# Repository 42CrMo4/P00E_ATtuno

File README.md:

# KiCad ATtuno Dev board

The ATtuno is a dev board for ATtiny 1 series microcontroller, loosely based on the UNO form factor. 

## Description

The ATtuno is an excellent starting point for those looking to explore the ATtiny 1 series microcontroller platform. 
Inspired by the familiar Arduino Uno form factor, this board offers a user-friendly approach to working with ATtiny Series 1 MCUs.
Key features:

- Arduino Uno-inspired layout
- Generous board size for comfortable handling
- Robust Wago clamping pin headers for secure connections
- Designed for quick start and rapid prototyping
- 3.3V and 5V compatible

This dev board bridges the gap between the popular Arduino ecosystem and the powerful, efficient ATtiny Series 1 microcontrollers. 
Its thoughtful design allows both beginners and experienced makers to quickly dive into projects without the need for delicate handling or specialized tools.

### Goal

The goal of the project will be:
- [ ] **undefined** - not known what the project will bring 
- [ ] **learn** - personally learn something new, no usefull outcome expected
- [ ] **prototype** - a working prototype or mvp
- [x] **80-20-rule** - 80% outcome with 20% effort
- [ ] **Product** - lets see :wink:

## KiCanvas 

view the project files in the browaser without downloading or installing anything via [KiCanvas](https://kicanvas.org)

[Main branche - Development](https://kicanvas.org/?github=https%3A%2F%2Fgithub.com%2F42CrMo4%2FP00E_ATtuno)

[v3.0](https://kicanvas.org/?github=https%3A%2F%2Fgithub.com%2F42CrMo4%2FP00E_ATtuno%2Ftree%2Fv3.0)

[v2.0](https://kicanvas.org/?github=https%3A%2F%2Fgithub.com%2F42CrMo4%2FP00E_ATtuno%2Ftree%2Fv2.0)

[v1.0](https://kicanvas.org/?github=https%3A%2F%2Fgithub.com%2F42CrMo4%2FP00E_ATtuno%2Ftree%2Fv1.0)

## Rendering (V3.0)

|     Font      |     Back      |
| ------------- | ------------- |
|||

If you are looking for the latest Release with all the artifacts please visit the 

## Rendering & BOM (Dev)

The renderings and BOM below are the uptodate state of the main branche.

| Font                                                                    | Back                                                                      |
|-------------------------------------------------------------------------|---------------------------------------------------------------------------|
|  |  |

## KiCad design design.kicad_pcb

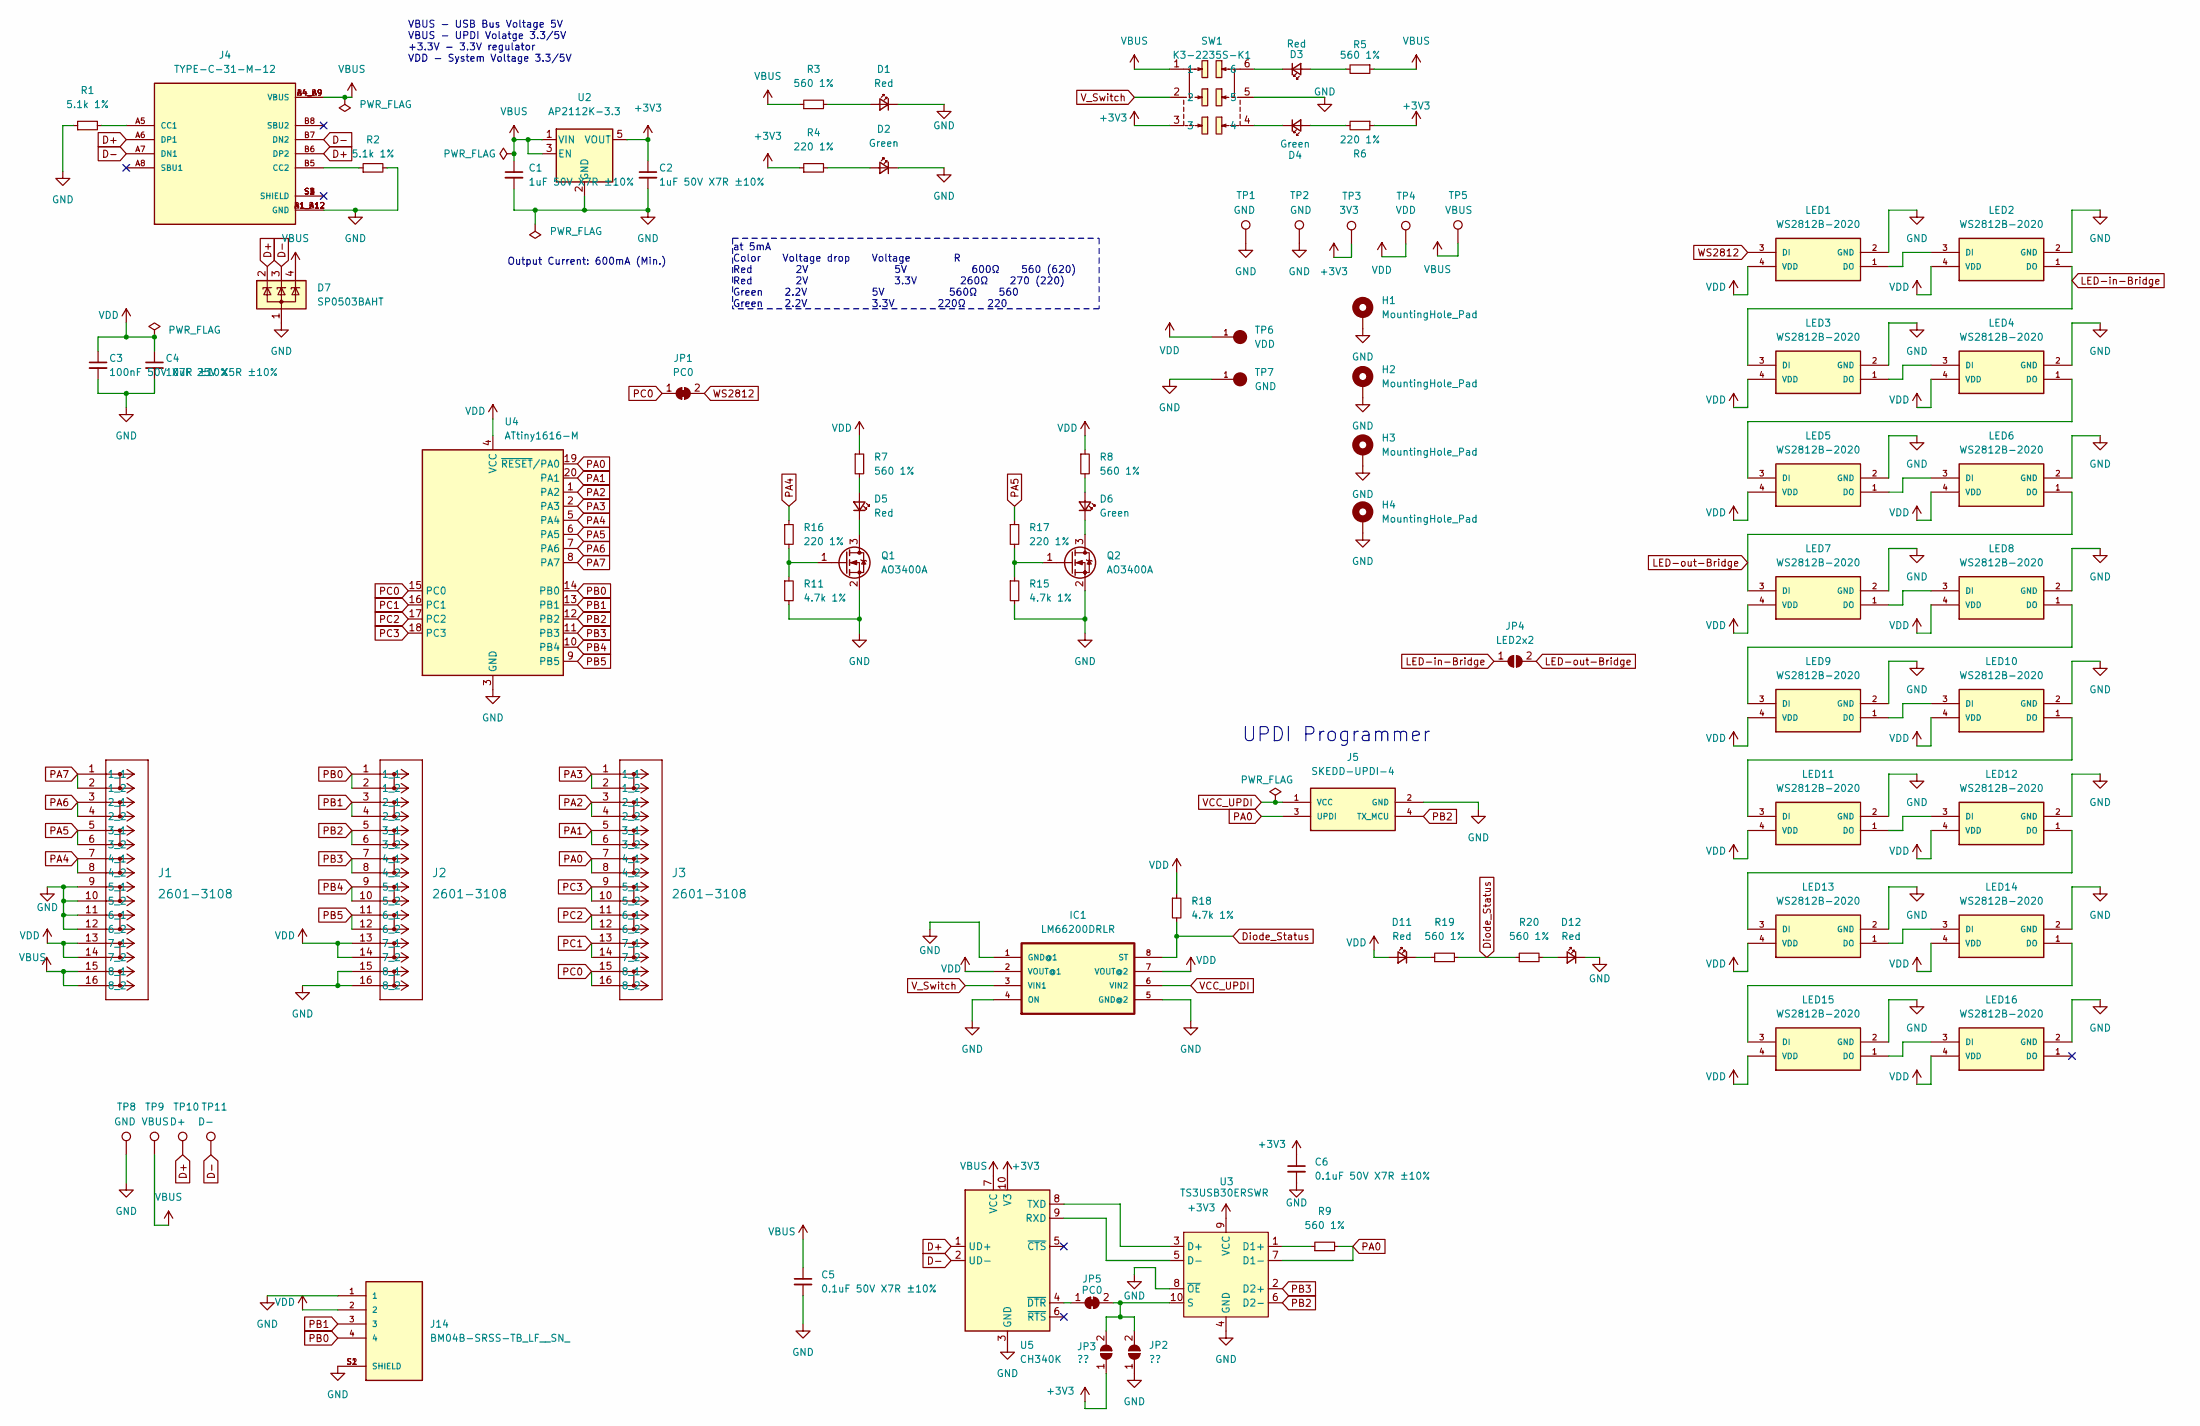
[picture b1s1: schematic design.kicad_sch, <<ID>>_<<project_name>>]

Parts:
C1, C2: 1uF 50V X7R ±10%; C_0805_2012Metric; MANUFACTURER_PART_NUMBER CL21B105KBFNNNE; JLCPCB C28323
C3: 100nF 50V X7R ±10%; C_0805_2012Metric; MANUFACTURER_PART_NUMBER CC0805KRX7R9BB104; JLCPCB C49678
C4: 10uF 25V X5R ±10%; C_0805_2012Metric; MANUFACTURER_PART_NUMBER CL21A106KAYNNNE; JLCPCB C15850
C5, C6: 0.1uF 50V X7R ±10%; C_0805_2012Metric; MANUFACTURER_PART_NUMBER CL21B105KBFNNNE; JLCPCB C28323
D1, D3, D5, D11, D12: Red; LED_0805_2012Metric; MANUFACTURER_PART_NUMBER NCD0805R1; JLCPCB C84256
D2, D4, D6: Green; LED_0805_2012Metric; MANUFACTURER_PART_NUMBER KT-0805G; JLCPCB C2297
D7: SP0503BAHT; SOT-143; MANUFACTURER_PART_NUMBER SP0503BAHTG; JLCPCB C3040626
H1, H2, H3, H4: MountingHole_Pad; MountingHole_2.7mm_M2.5_Pad_Via
IC1: LM66200DRLR; LM66200DRLR_SOT8
J1, J2, J3: 2601-3108; CONN8_2601-3108_WAG
J4: TYPE-C-31-M-12; TYPE-C-31-M-12_HRO_TYPE-C-31-M-12; PARTREV 2020.12.08; JLCPCB C165948
J5: SKEDD-UPDI-4
J14: BM04B-SRSS-TB_LF__SN_; BM04B-SRSS-TB_LF__SN__JST_BM04B-SRSS-TB_LF__SN_; PARTREV N/A; JLCPCB C160390
JP1, JP5: PC0; SolderJumper-2_P1.3mm_Bridged_Pad1.0x1.5mm
JP2, JP3: ??; SolderJumper-2_P1.3mm_Open_Pad1.0x1.5mm
JP4: LED2x2; SolderJumper-2_P1.3mm_Open_Pad1.0x1.5mm
LED1, LED2, LED3, LED4, LED5, LED6, LED7, LED8, LED9, LED10, LED11, LED12, LED13, LED14, LED15, LED16: WS2812B-2020; WS2812B2020; MANUFACTURER_PART_NUMBER WS2812B-2020; JLCPCB C965555
Q1, Q2: AO3400A; SOT-23; MANUFACTURER_PART_NUMBER AO3400A; JLCPCB C20917
R1, R2: 5.1k 1%; R_0805_2012Metric; MANUFACTURER_PART_NUMBER C27834; JLCPCB C27834
R3, R5, R7, R8, R9, R19, R20: 560 1%; R_0805_2012Metric; MANUFACTURER_PART_NUMBER 0805W8F5600T5E; JLCPCB C28636
R4, R6, R16, R17: 220 1%; R_0805_2012Metric; MANUFACTURER_PART_NUMBER 0805W8F2200T5E; JLCPCB C17557
R11, R15, R18: 4.7k 1%; R_0805_2012Metric; MANUFACTURER_PART_NUMBER 0805W8F4701T5E; JLCPCB C17673
SW1: K3-2235S-K1; easyeda2kicad_SW-SMD_K3-2235S-K1; MANUFACTURER_PART_NUMBER K3-2235S-K1; LCSC Part C145845
TP1, TP2, TP8: GND; TestPoint_Pad_D2.5mm
TP3: 3V3; TestPoint_Pad_D2.5mm
TP4: VDD; TestPoint_Pad_D2.5mm
TP5, TP9: VBUS; TestPoint_Pad_D2.5mm
TP6: VDD; RCWCTE_TP420X150; PARTREV 1/06/14
TP7: GND; RCWCTE_TP420X150; PARTREV 1/06/14
TP10: D+; TestPoint_Pad_D2.5mm
TP11: D-; TestPoint_Pad_D2.5mm
U2: AP2112K-3.3; SOT-23-5; MANUFACTURER_PART_NUMBER TPAP2112K-3.3TRG1; JLCPCB C3021085
U3: TS3USB30ERSWR; UQFN-10_1.4x1.8mm_P0.4mm
U4: ATtiny1616-M; ATTINY1616-MFR_QFN40P300X300X90-21N; MANUFACTURER_PART_NUMBER ATTINY1616-MNR; JLCPCB C507118
U5: CH340K; SSOP-10-1EP_3.9x4.9mm_P1mm_EP2.1x3.3mm

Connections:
+3V3: C2.1, C6.1, JP3.1 (A), R4.1, R6.1, SW1.3, TP3.1, U2.5 (VOUT), U3.9 (VCC), U5.10 (V3)
D+: D7.2 (K), J4.A6 (DP1), J4.B6 (DP2), TP10.1, U5.1 (UD+)
D-: D7.3 (K), J4.A7 (DN1), J4.B7 (DN2), TP11.1, U5.2 (UD-)
Diode_Status: IC1.8 (ST), R18.2, R19.2, R20.1
GND: C1.2, C2.2, C3.2, C4.2, C5.2, C6.2, D1.1 (K), D2.1 (K), D7.1 (A), D12.1 (K), H1.1, H2.1, H3.1, H4.1, IC1.1 (GND@1), IC1.4 (ON), IC1.5 (GND@2), J1.9 (5_1), J1.10 (5_2), J1.11 (6_1), J1.12 (6_2), J2.15 (8_1), J2.16 (8_2), J4.A1_B12 (GND), J4.B1_A12 (GND), J5.2 (GND), J14.1, J14.S1 (SHIELD), J14.S2 (SHIELD), JP2.1 (A), LED1.2 (GND), LED2.2 (GND), LED3.2 (GND), LED4.2 (GND), LED5.2 (GND), LED6.2 (GND), LED7.2 (GND), LED8.2 (GND), LED9.2 (GND), LED10.2 (GND), LED11.2 (GND), LED12.2 (GND), LED13.2 (GND), LED14.2 (GND), LED15.2 (GND), LED16.2 (GND), Q1.2 (S), Q2.2 (S), R1.1, R2.2, R11.2, R15.2, SW1.5, TP1.1, TP2.1, TP7.1, TP8.1, U2.2 (GND), U3.4 (GND), U3.8 (~OE), U4.3 (GND), U4.21 (GND), U5.3 (GND), U5.11 (GND)
LED-in-Bridge: JP4.1 (A), LED2.1 (DO), LED3.3 (DI)
LED-out-Bridge: JP4.2 (B), LED6.1 (DO), LED7.3 (DI)
unnamed: D1.2 (A), R3.2
unnamed: D2.2 (A), R4.2
unnamed: D3.2 (A), R5.2
unnamed: D3.1 (K), SW1.6
unnamed: D4.2 (A), R6.2
unnamed: D4.1 (K), SW1.4
unnamed: D5.2 (A), R7.2
unnamed: D5.1 (K), Q1.3 (D)
unnamed: D6.2 (A), R8.2
unnamed: D6.1 (K), Q2.3 (D)
unnamed: D11.1 (K), R19.1
unnamed: D12.2 (A), R20.2
unnamed: J4.A5 (CC1), R1.2
unnamed: J4.B5 (CC2), R2.1
unnamed: JP2.2 (B), JP3.2 (B), JP5.2 (B), U3.10 (S)
unnamed: JP5.1 (A), U5.4 (~DTR)
unnamed: LED1.1 (DO), LED2.3 (DI)
unnamed: LED3.1 (DO), LED4.3 (DI)
unnamed: LED4.1 (DO), LED5.3 (DI)
unnamed: LED5.1 (DO), LED6.3 (DI)
unnamed: LED7.1 (DO), LED8.3 (DI)
unnamed: LED8.1 (DO), LED9.3 (DI)
unnamed: LED9.1 (DO), LED10.3 (DI)
unnamed: LED10.1 (DO), LED11.3 (DI)
unnamed: LED11.1 (DO), LED12.3 (DI)
unnamed: LED12.1 (DO), LED13.3 (DI)
unnamed: LED13.1 (DO), LED14.3 (DI)
unnamed: LED14.1 (DO), LED15.3 (DI)
unnamed: LED15.1 (DO), LED16.3 (DI)
unnamed: Q1.1 (G), R11.1, R16.2
unnamed: Q2.1 (G), R15.1, R17.2
unnamed: R9.1, U3.1 (D1+)
unnamed: U3.3 (D+), U5.8 (TXD)
unnamed: U3.5 (D-), U5.9 (RXD)
PA0: J3.7 (4_1), J3.8 (4_2), J5.3 (UPDI), R9.2, U3.7 (D1-), U4.19 (~RESET/PA0)
PA1: J3.5 (3_1), J3.6 (3_2), U4.20 (PA1)
PA2: J3.3 (2_1), J3.4 (2_2), U4.1 (PA2)
PA3: J3.1 (1_1), J3.2 (1_2), U4.2 (PA3)
PA4: J1.7 (4_1), J1.8 (4_2), R16.1, U4.5 (PA4)
PA5: J1.5 (3_1), J1.6 (3_2), R17.1, U4.6 (PA5)
PA6: J1.3 (2_1), J1.4 (2_2), U4.7 (PA6)
PA7: J1.1 (1_1), J1.2 (1_2), U4.8 (PA7)
PB0: J2.1 (1_1), J2.2 (1_2), J14.4, U4.14 (PB0)
PB1: J2.3 (2_1), J2.4 (2_2), J14.3, U4.13 (PB1)
PB2: J2.5 (3_1), J2.6 (3_2), J5.4 (TX_MCU), U3.6 (D2-), U4.12 (PB2)
PB3: J2.7 (4_1), J2.8 (4_2), U3.2 (D2+), U4.11 (PB3)
PB4: J2.9 (5_1), J2.10 (5_2), U4.10 (PB4)
PB5: J2.11 (6_1), J2.12 (6_2), U4.9 (PB5)
PC0: J3.15 (8_1), J3.16 (8_2), JP1.1 (A), U4.15 (PC0)
PC1: J3.13 (7_1), J3.14 (7_2), U4.16 (PC1)
PC2: J3.11 (6_1), J3.12 (6_2), U4.17 (PC2)
PC3: J3.9 (5_1), J3.10 (5_2), U4.18 (PC3)
VBUS: C1.1, C5.1, D7.4 (K), J1.15 (8_1), J1.16 (8_2), J4.A4_B9 (VBUS), J4.B4_A9 (VBUS), R3.1, R5.1, SW1.1, TP5.1, TP9.1, U2.1 (VIN), U2.3 (EN), U5.7 (VCC)
VCC_UPDI: IC1.6 (VIN2), J5.1 (VCC)
VDD: C3.1, C4.1, D11.2 (A), IC1.2 (VOUT@1), IC1.7 (VOUT@2), J1.13 (7_1), J1.14 (7_2), J2.13 (7_1), J2.14 (7_2), J14.2, LED1.4 (VDD), LED2.4 (VDD), LED3.4 (VDD), LED4.4 (VDD), LED5.4 (VDD), LED6.4 (VDD), LED7.4 (VDD), LED8.4 (VDD), LED9.4 (VDD), LED10.4 (VDD), LED11.4 (VDD), LED12.4 (VDD), LED13.4 (VDD), LED14.4 (VDD), LED15.4 (VDD), LED16.4 (VDD), R7.1, R8.1, R18.1, TP4.1, TP6.1, U4.4 (VCC)
V_Switch: IC1.3 (VIN1), SW1.2
WS2812: JP1.2 (B), LED1.3 (DI)

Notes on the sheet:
VBUS - USB Bus Voltage 5V VBUS - UPDI Volatge 3.3/5V +3.3V - 3.3V regulator VDD - System Voltage 3.3/5V
at 5mA Color Voltage drop Voltage R Red 2V 5V 600Ω 560 (620) Red 2V 3.3V 260Ω 270 (220) Green 2.2V 5V 560Ω 560 Green 2.2V 3.3V 220Ω 220
Output Current: 600mA (Min.)
UPDI Programmer

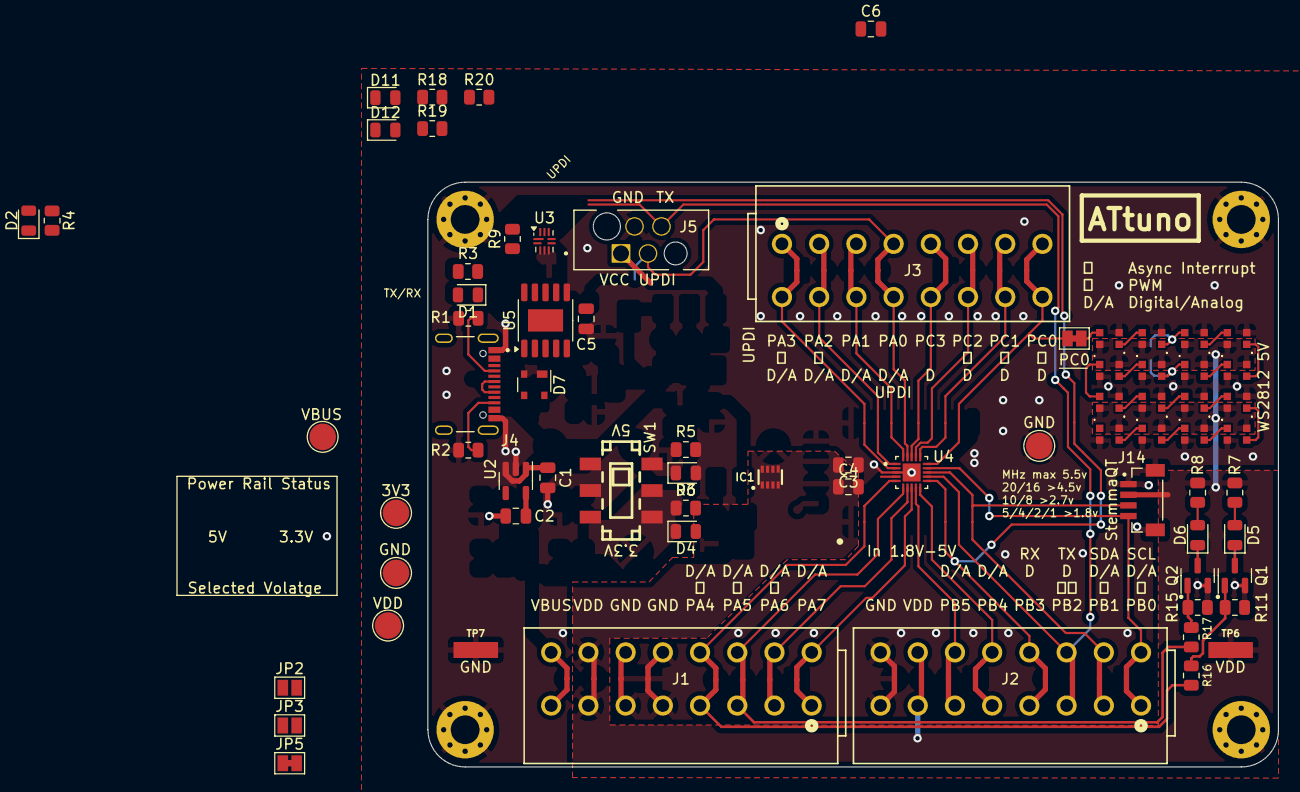
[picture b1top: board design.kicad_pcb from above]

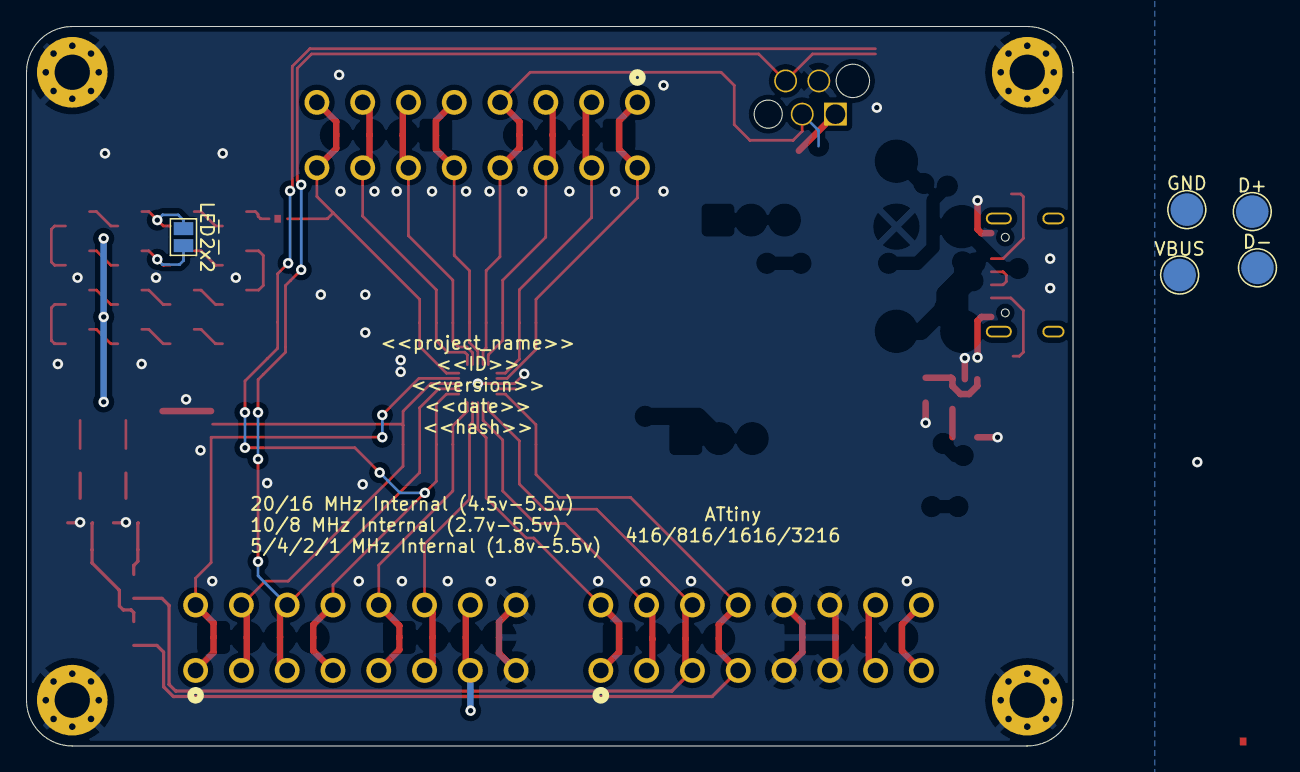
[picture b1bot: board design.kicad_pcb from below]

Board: 2 copper layers, 80.0 x 55.0 mm, 81 parts (5 on the bottom side), 64 nets.

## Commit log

2024-09-07 setup the repo
2024-10-03 many changes
2024-10-06 lot of updates
2024-10-06 update edge layer
2024-10-06 add 3D files
2024-10-06 DEL unneeded 3D File
2024-10-06 new stuff
2024-10-06 DEL unneeded
2024-10-06 ERC correction
    Warnings are everywhere
2024-10-06 DRC correction
2024-10-06 Archive & Renew release docs
2024-10-06 mirror property text on the back, remove weblink
2024-10-06 Update Bom and PCB_top
2024-10-21 small updates
    silkscreen update,
    via not over silkscreen,
    connect GND planes
2024-10-21 connect ground plane by moving routing
2024-10-23 SCH additions
    Mounting holes
    Test Pads
    01x04 pinheaders
2024-10-23 ADD CP2105
    Add a new USB2UART Sheet
2024-10-23 remove subsheet USB2UART
2024-10-25 SCH add designator and footprints
2024-11-02 fake change
2024-11-02 escaped delimiter '/'
2024-11-02 many updates
2024-11-03 cleanup
2024-11-03 KiPlot use correct zoom level
2024-11-03 consolidate traces
2024-11-03 add LED color and Parameters
2024-11-03 Add TVS Diode to USB
2024-11-03 add GND via cp2105
2024-11-03 change to BM04B-SRSS-TB symbol
2024-11-03 update LED resistor values
2024-11-03 use v6.x workflow branch?
2024-11-03 change LEDs to pin PB2/PB3 not to use the i2c pins
2024-11-03 update checklist and release notes
2024-11-04 findall instead of finiter?
2024-11-04 debug print matches
2024-11-04 run on yml change too
2024-11-04 diffrent approach
2024-11-04 Revert "diffrent approach"
    This reverts commit bcd978d2fc3cbf98be5c890396496ee4c0d68544.
2024-11-04 move files and path
2024-11-04 no pyyml
2024-11-04 update actions
2024-11-04 Add workflow to find missing 3d models (#1)
2024-11-13 Route LEDs to own pins
    closes #2
    Use PA4 and PA5 for the LEDs. This pins have PWM and are not used.
    correct the silk screen.
2024-11-13 fix VDD plane
2024-11-13 Arrange TestPoints in a grid. Correct small traces.
2024-11-13 update silkscreen
2024-11-13 use switchable power input for CP2105
    closes #3
    is not compatible with header pins only on J12
2024-11-13 move C2 closer to U2
2024-11-13 small trace fix
2024-11-13 align R1/R2 around USB connector
2024-11-13 correct DRC issues
2024-11-14 add CP2105 VBus solderbridge
    closes #5
2024-11-15 add programming capacitor
    closes #4
    to use the TX/RX LEDs the cp2105 must be programmed to use this function (only one time possible). Todo this a 4,7uF capacitor must be used on pin VPP according to the Datasheet Note 4 page 18.
2024-11-15 add designators
2024-11-15 add note for jp5
2024-11-15 Add USB Programming interface
    Touchpoints on Back for USB, Power and VPP.
    VPP so the 4,7uF capacitor must not be populated and can be done with a programming rig.
2024-11-15 Add Silkscreen update
    Add information to the front.
    update various information.
    arrange it more neatly.
2024-11-15 Updates testpoints
    make them align on full intervals
    add dimension marker
2024-11-15 Add ATtiny QFN
2024-11-15 small minor updates
    DRC issues
    make traces lean
2024-11-17 add JLCPCB
2024-11-17 add component information
    capacitor additional values
    JLCPCB part #
2024-11-24 change to K3-2235S-K1 / JS202011SCQN DPDT Switch
2024-11-24 Add MOSFET for GPIO LEDs
2024-11-24 Add Gate Resistor MOSFET
2024-11-24 add the workflow files & update Kibot 1.8.2
2024-11-24 add Variants
2024-11-24 add LCSC numbers to correct column
2024-11-24 change to snapeda Footprint for QFN Attiny
2024-11-25 test kiauto8
2024-11-25 Revert "test kiauto8"
    This reverts commit 07679f853a7057e5708bba1d94cd474b366312e4.
2024-11-25 remove via
2024-11-26 _JLCPCB output?
2024-11-26 use groups in kobot
2024-11-26 use variants via kiplot.yaml yq
2024-11-26 no sudo
2024-11-26 typo
2024-11-30 add JLCPCB to (rc)release
    _JLCPCB_compress _JLCPCB_assembly
2024-11-30 add v2.0 Diffs
2024-11-30 use unique naming
2024-11-30 add PCBWAY
2024-11-30 add output names
2024-11-30 add pin1 marker
2024-11-30 add Mfg Part #
2024-11-30 add position output
2024-11-30 add position output (rc)release
2024-11-30 typo output format
2024-11-30 add extension
2024-11-30 add resistor variance
2024-11-30 add variant default to (rc)release
2024-11-30 DFM Check updates
2024-11-30 ad variant to all (rc)release outputs
2024-11-30 fill PCB
2024-12-01 DEL uneeded code
2024-12-01 refactor variable replacement in kicad files
2024-12-01 disable STEP generation
2024-12-01 add group generation_output
2024-12-01 disable SOIC Variant
2024-12-01 add Kicanvas Links
2024-12-01 add spacing
2024-12-01 correct Link format
2024-12-01 remove new line
2024-12-01 Refactor WF and use Groups for outputs (#6)
    * DEL uneeded code
    * refactor variable replacement in kicad files
    * disable STEP generation
    * add group generation_output
    * disable SOIC Variant
    * remove new line
2024-12-06 print footprint values in jlcpcb
2024-12-06 Revert "print footprint values in jlcpcb"
    This reverts commit 624751174857fc160f60b685ec09f43c98517ca8.
2024-12-06 use definitions:
2024-12-06 JlC plot fiix (#8)
    * use definitions:
2024-12-22 add basic Arduino sketch
2025-04-03 add LM66200DRLR
2025-06-21 update to v9
2025-07-20 allot
2025-07-20 add Diff to v3.1
2025-07-20 Diff to v3.1 part 2
2025-07-20 DEL SOIC ATtiny
2025-07-20 DEL all 2.54 pinheader
2025-07-20 lot of changes
2025-07-20 add LM66200DRLR.step
2025-07-21 some more some
